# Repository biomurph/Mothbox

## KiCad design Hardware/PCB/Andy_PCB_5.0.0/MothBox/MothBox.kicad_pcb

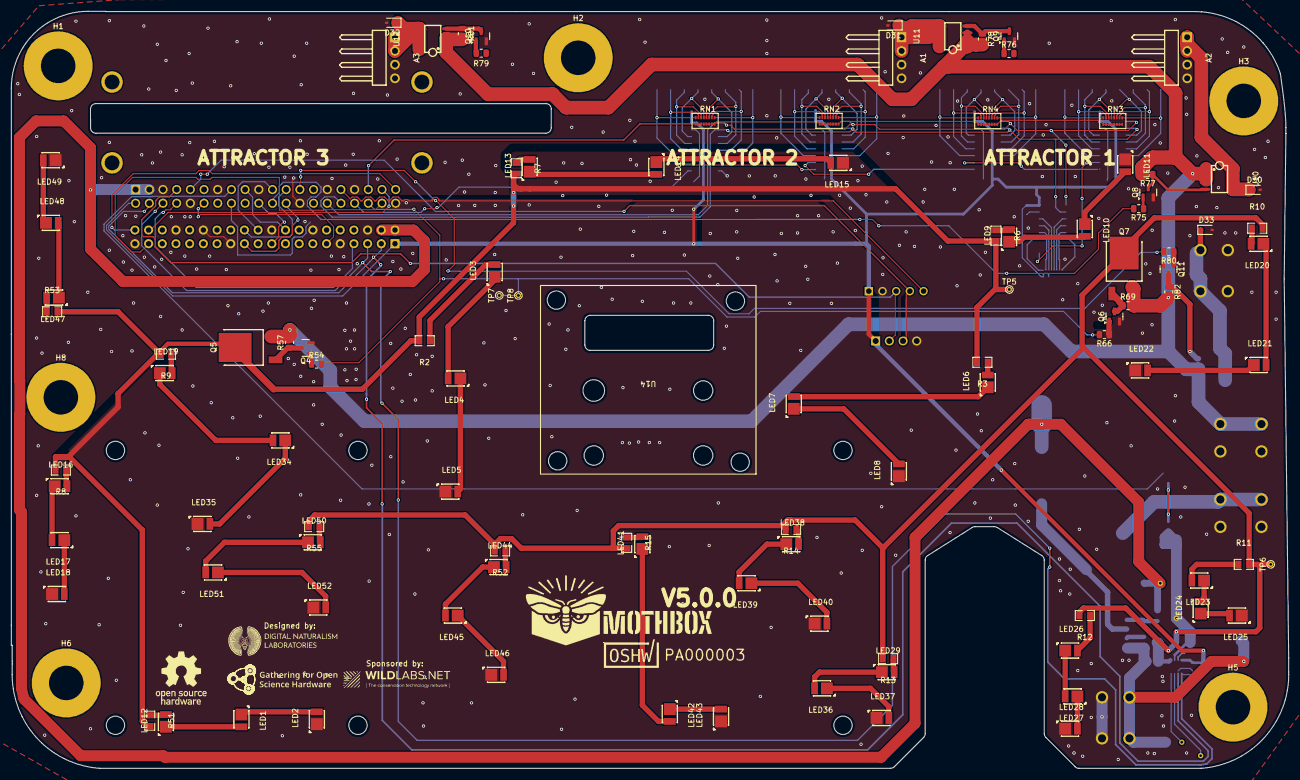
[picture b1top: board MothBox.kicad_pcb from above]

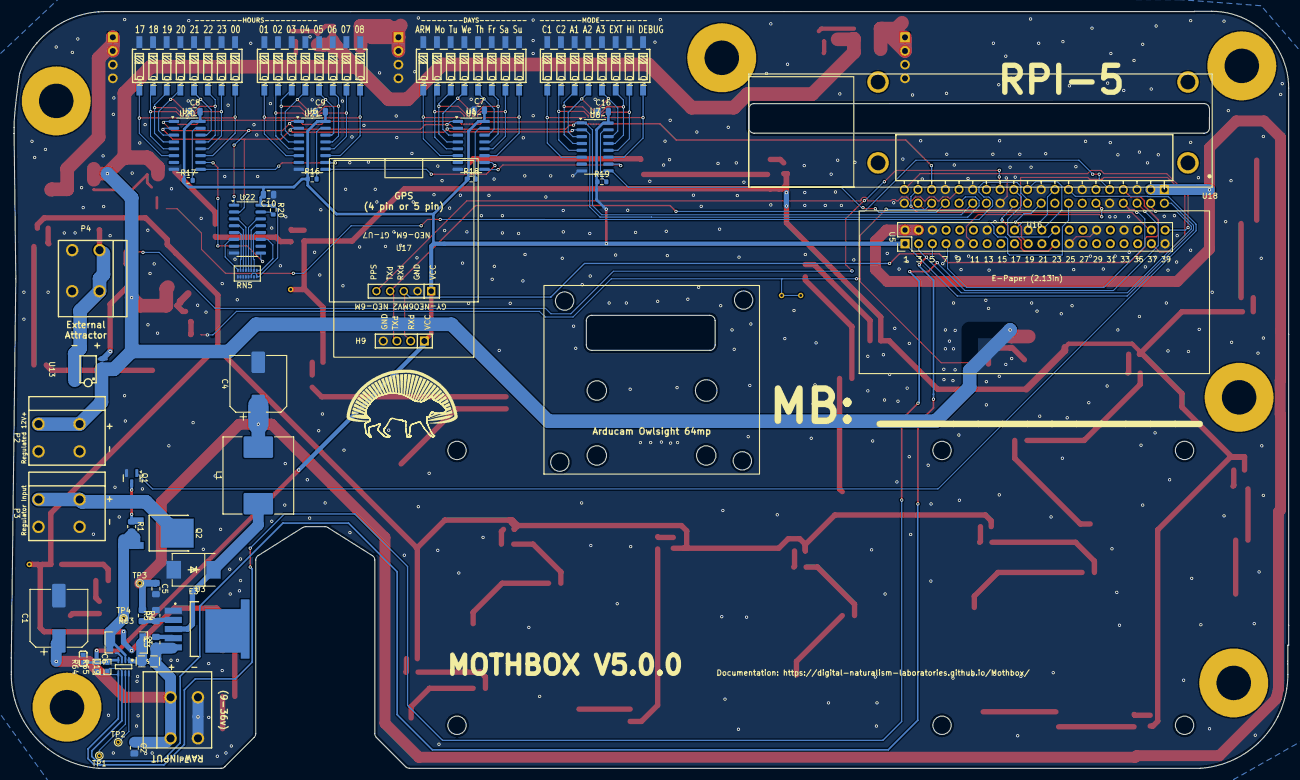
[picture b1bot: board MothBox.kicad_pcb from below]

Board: 2 copper layers, 237.0 x 140.5 mm, 163 parts (54 on the bottom side), 152 nets.

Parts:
A1, A2, A3: PZ254R-11-04P; HDR-TH_4P-P2.54-H-M-W10.4
B1: Talentcell
C1: 470uF 50V; CP_Elec_10x12.5
C2, C3, C5: 0.1uF 50V; C_0805_2012Metric_Pad1.18x1.45mm_HandSolder
C4: 330uF 50V; CP_Elec_10x10
C6: 0.1µF; C0603
C7, C8, C9, C10, C16: 0.1uF; C_0805_2012Metric
D30, D31, D32, D33: ESD12VD3B-TP; D_SOD-323
E3: SK54C; SMC_L6.9-W5.9-LS8.0-RD
F2: Polyfuse; F0805
H1, H2, H3, H5, H6, H8: MountingHole_1/4inbolt; MountingHole_6.4mm_M6_Pad
H9: GPS 4 pin 2.54-1*4P母; GPS4pin_HDR-TH_4P-P2.54-V-F
L1: 5A 47uH; L_Chilisin_BMRG00131360
LED1, LED2, LED3, LED4, LED5, LED6, LED7, LED8, LED9, LED10, LED11, LED12, LED13, LED14, LED15, LED16, LED17, LED18, LED19, LED20, LED21, LED22, LED23, LED24, LED25, LED26, LED27, LED28, LED29, LED34, LED35, LED36, LED37, LED38, LED39, LED40, LED41, LED42, LED43, LED44, LED45, LED46, LED47, LED48, LED49, LED50, LED51, LED52: XL-2835UWC-02; LED-SMD_L3.5-W2.8-RD_1.25T-2PWT
P1: Raw Input; CONN-TH_2P-P5.08_DIBO_DB142R-5.08-2P
P2: 12V Regulated Input; CONN-TH_2P-P5.08_DIBO_DB142R-5.08-2P
P3: Input to regulator; CONN-TH_2P-P5.08_DIBO_DB142R-5.08-2P
P4: External Attractor; CONN-TH_2P-P5.08_DIBO_DB142R-5.08-2P
Q1, Q4, Q6, Q8, Q9, Q10, Q11: BC817; SOT-23
Q2, Q5, Q7: SUD50P06-15-GE3; TO-252-3_L6.5-W5.8-P4.58-BL
R1, R57, R69, R77, R78, R81, R82: 10k; R_0805_2012Metric
R2, R3, R6, R7, R8, R9, R10, R11, R12, R13, R14, R15, R51, R52, R53, R55: FRC0805F30R0TS; R0805
R4: 10K; C_0805_2012Metric_Pad1.18x1.45mm_HandSolder
R5: 3.3K; C_0805_2012Metric_Pad1.18x1.45mm_HandSolder
R16, R17, R18, R19, R20: 100K; R_0603_1608Metric
R54, R66, R75, R76, R79, R80: 1k; R_0805_2012Metric
R63: 0.1/1% (PT2512FK-070R1L); R2512
R64, R65: 10k; R0603
RN1, RN2, RN3, RN4, RN5: 100K; 16P8-R-Array
TP1: A0_meas; TestPoint_THTPad_D1.0mm_Drill0.5mm
TP2: A1_meas; TestPoint_THTPad_D1.0mm_Drill0.5mm
TP3: 5V_test; TestPoint_THTPad_D1.0mm_Drill0.5mm
TP4: VIN_-; TestPoint_THTPad_D1.0mm_Drill0.5mm
TP5: +12VLED L; TestPoint_THTPad_D1.0mm_Drill0.5mm
TP6: +12VLED R; TestPoint_THTPad_D1.0mm_Drill0.5mm
TP7: LEDCTRL_L; TestPoint_THTPad_D1.0mm_Drill0.5mm
TP8: LEDCTRL_R; TestPoint_THTPad_D1.0mm_Drill0.5mm
U1: Days; SW-SMD_SMXS-08K-TP
U2: Hours1; SW-SMD_SMXS-08K-TP
U3: XL4015E1; TO-263-5_L10.2-W8.9-P1.70-TL
U5: RASPBERRY_PI_5; EPAPER_PinHeader_2x20_P2.54mm_Vertical
U6: Hours2; SW-SMD_SMXS-08K-TP
U7: Modes; SW-SMD_SMXS-08K-TP
U8, U9, U20, U21, U22: 74HC165; SOIC-16_3.9x9.9mm_P1.27mm
U10, U11, U12, U13: FDS4435BZ; SOIC-8_L5.0-W4.0-P1.27-LS6.0-BL
U14: Arducam Owlsight
U16: Female Inv Socket Pi 2.54-2*20; HDR-TH_40P-P2.54-H-F-R2-C20-W8.5
U17: GPs 5 pin PM2.54-1*5; GPS5pin_HDR-TH_5P-P2.54-V-F
U18: RASPBERRY_PI_4B_4GB; MODULE_RASPBERRY_PI_4B_4GB_Sideways
U19: INA219BIDCNT; SOT-23-8_L3.0-W1.7-P0.65-LS2.8-BR

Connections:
+3.3V: C6.2, C7.2, C8.2, C9.2, C10.2, C16.2, H9.1, R16.1, R17.1, R18.1, R19.1, R20.1, R64.2, R65.2, RN5.6 (R6.1), RN5.8 (R8.1), U5.1 (3V3), U8.16 (VCC), U9.16 (VCC), U16.2, U17.1, U19.4 (VS), U20.16 (VCC), U21.16 (VCC), U22.16 (VCC)
+5V: C4.1, C5.1, L1.2, R4.1, TP3.1, U5.2 (5V), U5.4 (5V), U16.1, U16.3
+12V: P2.2, Q5.3 (S), Q7.3 (S), R57.2, R69.2, R77.2, R78.2, R81.2, R82.2, U10.1 (S), U10.2 (S), U10.3 (S), U11.1 (S), U11.2 (S), U11.3 (S), U12.1 (S), U12.2 (S), U12.3 (S), U13.1 (S), U13.2 (S), U13.3 (S)
+24V: C1.1, C2.1, C3.1, F2.2, P1.2, U3.5 (VIN)
/GPS and Switches/Armed/Disarmed: RN2.8 (R8.1), U1.16, U9.11 (D0)
/GPS and Switches/Attractor_1: RN1.3 (R3.1), U7.11, U8.4 (D5)
/GPS and Switches/Attractor_2: RN1.4 (R4.1), U7.12, U8.3 (D4)
/GPS and Switches/Attractor_3: RN1.5 (R5.1), U7.13, U8.14 (D3)
/GPS and Switches/B0: RN5.9 (R8.2), U22.11 (D0)
/GPS and Switches/B1: RN5.10 (R7.2), U22.12 (D1)
/GPS and Switches/B2: RN5.11 (R6.2), U22.13 (D2)
/GPS and Switches/B3: RN5.12 (R5.2), U22.14 (D3)
/GPS and Switches/B4: RN5.13 (R4.2), U22.3 (D4)
/GPS and Switches/B5: RN5.14 (R3.2), U22.4 (D5)
/GPS and Switches/B6: RN5.15 (R2.2), U22.5 (D6)
/GPS and Switches/B7: RN5.16 (R1.2), U22.6 (D7)
/GPS and Switches/C1: RN1.1 (R1.1), U7.9, U8.6 (D7)
/GPS and Switches/C2: RN1.2 (R2.1), U7.10, U8.5 (D6)
/GPS and Switches/Fri: RN2.3 (R3.1), U1.11, U9.4 (D5)
/GPS and Switches/HI/LOW_PWR: RN1.7 (R7.1), U7.15, U8.12 (D1)
/GPS and Switches/Hour_1: RN3.1 (R1.1), U2.9, U20.6 (D7)
/GPS and Switches/Hour_2: RN3.2 (R2.1), U2.10, U20.5 (D6)
/GPS and Switches/Hour_3: RN3.3 (R3.1), U2.11, U20.4 (D5)
/GPS and Switches/Hour_4: RN3.4 (R4.1), U2.12, U20.3 (D4)
/GPS and Switches/Hour_5: RN3.5 (R5.1), U2.13, U20.14 (D3)
/GPS and Switches/Hour_6: RN3.6 (R6.1), U2.14, U20.13 (D2)
/GPS and Switches/Hour_7: RN3.7 (R7.1), U2.15, U20.12 (D1)
/GPS and Switches/Hour_8: RN3.8 (R8.1), U2.16, U20.11 (D0)
/GPS and Switches/Hour_9: RN4.1 (R1.1), U6.9, U21.6 (D7)
/GPS and Switches/Hour_10: RN4.2 (R2.1), U6.10, U21.5 (D6)
/GPS and Switches/Hour_11: RN4.3 (R3.1), U6.11, U21.4 (D5)
/GPS and Switches/Hour_12: RN4.4 (R4.1), U6.12, U21.3 (D4)
/GPS and Switches/Hour_13: RN4.5 (R5.1), U6.13, U21.14 (D3)
/GPS and Switches/Hour_14: RN4.6 (R6.1), U6.14, U21.13 (D2)
/GPS and Switches/Hour_15: RN4.7 (R7.1), U6.15, U21.12 (D1)
/GPS and Switches/Hour_16: RN4.8 (R8.1), U6.16, U21.11 (D0)
/GPS and Switches/INT/EXT_Attractor: RN1.6 (R6.1), U7.14, U8.13 (D2)
/GPS and Switches/Mon: RN2.7 (R7.1), U1.15, U9.12 (D1)
/GPS and Switches/Sat: RN2.2 (R2.1), U1.10, U9.5 (D6)
/GPS and Switches/Sun: RN2.1 (R1.1), U1.9, U9.6 (D7)
/GPS and Switches/Test_Debug: RN1.8 (R8.1), U7.16, U8.11 (D0)
/GPS and Switches/Thur: RN2.4 (R4.1), U1.12, U9.3 (D4)
/GPS and Switches/Tue: RN2.6 (R6.1), U1.14, U9.13 (D2)
/GPS and Switches/U9_OUT: U8.10 (DS), U9.9 (Q7)
/GPS and Switches/U20_OUT: U20.9 (Q7), U21.10 (DS)
/GPS and Switches/U21_OUT: U9.10 (DS), U21.9 (Q7)
/GPS and Switches/U22_OUT: U20.10 (DS), U22.9 (Q7)
/GPS and Switches/Wed: RN2.5 (R5.1), U1.13, U9.14 (D3)
/Photo LED's/+12V_L_LED: Q5.2 (D), R2.2, R3.2, R6.2, R7.2, R8.2, R9.2, R51.2, R53.2, TP5.1
/Photo LED's/+12V_R_LED: Q7.2 (D), R10.2, R11.2, R12.2, R13.2, R14.2, R15.2, R52.2, R55.2, TP6.1
/Power/FB: R4.2, R5.1, U3.2 (FB)
/Power/VIN+: F2.1, R63.2, U19.1 (IN+)
/Power/VIN-: Q2.3 (S), R1.2, R63.1, TP4.1, U19.2 (IN-)
/RPI5/GPIO4/GPIO_GCKL: U5.7 (GPIO4/GPIO_GCKL), U16.8
/RPI5/Save for eink_11: U5.11 (GPIO17/GPIO_GEN0), U16.12
/RPI5/Save for eink_18: U5.18 (GPIO24/GPIO_GEN5), U16.17
/RPI5/Save for eink_19: U5.19 (GPIO10/SPI_MOSI), U16.20
/RPI5/Save for eink_22: U5.22 (GPIO25/GPIO_GEN6), U16.21
/RPI5/Save for eink_23: U5.23 (GPIO11/SPI_SCLK), U16.24
/RPI5/Save for eink_24: U5.24 (GPIO8/~SPI_CE0), U16.23
/RPI5/Save for relay: U5.38 (GPIO20), U16.37
/RPI5/Save for relay 2: U5.40 (GPIO21), U16.39
/RPI5/Save for relay 3: U5.37 (GPIO26), U16.38
/UV LED PCB/+12V_PCB1: A2.1, A2.2, D30.1 (K), U10.5 (D), U10.6 (D), U10.7 (D), U10.8 (D)
/UV LED PCB/+12V_PCB2: A1.1, A1.2, D31.1 (K), U11.5 (D), U11.6 (D), U11.7 (D), U11.8 (D)
/UV LED PCB/+12V_PCB3: A3.1, A3.2, D32.1 (K), U12.5 (D), U12.6 (D), U12.7 (D), U12.8 (D)
/UV LED PCB/+12V_PCB4: D33.1 (K), P4.2, U13.5 (D), U13.6 (D), U13.7 (D), U13.8 (D)
EN_12VReg: Q1.1 (B), U16.15
GND: A1.3, A1.4, A2.3, A2.4, A3.3, A3.4, C1.2, C2.2, C4.2, C5.2, C6.1, C7.1, C8.1, C9.1, C10.1, C16.1, D30.2 (A), D31.2 (A), D32.2 (A), D33.2 (A), E3.2 (A), H9.4, LED2.1 (K), LED5.1 (K), LED8.1 (K), LED11.1 (K), LED15.1 (K), LED18.1 (K), LED22.1 (K), LED25.1 (K), LED28.1 (K), LED35.1 (K), LED37.1 (K), LED40.1 (K), LED43.1 (K), LED46.1 (K), LED49.1 (K), LED52.1 (K), P1.1, P2.1, P3.1, P4.1, Q1.2 (E), Q4.2 (E), Q6.2 (E), Q8.2 (E), Q9.2 (E), Q10.2 (E), Q11.2 (E), R5.2, RN5.1 (R1.1), RN5.2 (R2.1), RN5.3 (R3.1), RN5.4 (R4.1), RN5.5 (R5.1), RN5.7 (R7.1), U1.1, U1.2, U1.3, U1.4, U1.5, U1.6, U1.7, U1.8, U2.1, U2.2, U2.3, U2.4, U2.5, U2.6, U2.7, U2.8, U3.1 (GND), U5.6 (GND), U5.9 (GND), U5.14 (GND), U5.20 (GND), U5.25 (GND), U5.30 (GND), U5.34 (GND), U5.39 (GND), U6.1, U6.2, U6.3, U6.4, U6.5, U6.6, U6.7, U6.8, U7.1, U7.2, U7.3, U7.4, U7.5, U7.6, U7.7, U7.8, U8.8 (GND), U9.8 (GND), U16.5, U16.10, U16.13, U16.19, U16.26, U16.29, U16.33, U16.40, U17.2, U19.3 (GND), U20.8 (GND), U21.8 (GND), U22.8 (GND)
GPS_PPS: U16.31, U17.5
GPS_RX: H9.2, U16.7, U17.3
GPS_TX: H9.3, U16.9, U17.4
L_LED_CTRL: R54.2, R66.2, TP7.1, TP8.1, U16.36
unnamed: E3.1 (C), L1.1, U3.3 (SW)
unnamed: LED1.2 (A), LED12.1 (K)
unnamed: LED1.1 (K), LED2.2 (A)
unnamed: LED3.2 (A), R2.1
unnamed: LED3.1 (K), LED4.2 (A)
unnamed: LED4.1 (K), LED5.2 (A)
unnamed: LED6.2 (A), R3.1
unnamed: LED6.1 (K), LED7.2 (A)
unnamed: LED7.1 (K), LED8.2 (A)
unnamed: LED9.2 (A), R6.1
unnamed: LED9.1 (K), LED10.2 (A)
unnamed: LED10.1 (K), LED11.2 (A)
unnamed: LED12.2 (A), R51.1
unnamed: LED13.2 (A), R7.1
unnamed: LED13.1 (K), LED14.2 (A)
unnamed: LED14.1 (K), LED15.2 (A)
unnamed: LED16.2 (A), R8.1
unnamed: LED16.1 (K), LED17.2 (A)
unnamed: LED17.1 (K), LED18.2 (A)
unnamed: LED19.2 (A), R9.1
unnamed: LED19.1 (K), LED34.2 (A)
unnamed: LED20.2 (A), R10.1
unnamed: LED20.1 (K), LED21.2 (A)
unnamed: LED21.1 (K), LED22.2 (A)
unnamed: LED23.2 (A), R11.1
unnamed: LED23.1 (K), LED24.2 (A)
unnamed: LED24.1 (K), LED25.2 (A)
unnamed: LED26.2 (A), R12.1
unnamed: LED26.1 (K), LED27.2 (A)
unnamed: LED27.1 (K), LED28.2 (A)
unnamed: LED29.2 (A), R13.1
unnamed: LED29.1 (K), LED36.2 (A)
unnamed: LED34.1 (K), LED35.2 (A)
unnamed: LED36.1 (K), LED37.2 (A)
unnamed: LED38.2 (A), R14.1
unnamed: LED38.1 (K), LED39.2 (A)
unnamed: LED39.1 (K), LED40.2 (A)
unnamed: LED41.2 (A), R15.1
unnamed: LED41.1 (K), LED42.2 (A)
unnamed: LED42.1 (K), LED43.2 (A)
unnamed: LED44.2 (A), R52.1
unnamed: LED44.1 (K), LED45.2 (A)
unnamed: LED45.1 (K), LED46.2 (A)
unnamed: LED47.2 (A), R53.1
unnamed: LED47.1 (K), LED48.2 (A)
unnamed: LED48.1 (K), LED49.2 (A)
unnamed: LED50.2 (A), R55.1
unnamed: LED50.1 (K), LED51.2 (A)
unnamed: LED51.1 (K), LED52.2 (A)
unnamed: Q1.3 (C), Q2.1 (G), R1.1
unnamed: P3.2, Q2.2 (D)
unnamed: Q4.1 (B), R54.1
unnamed: Q4.3 (C), Q5.1 (G), R57.1
unnamed: Q6.1 (B), R66.1
unnamed: Q6.3 (C), Q7.1 (G), R69.1
unnamed: Q8.1 (B), R75.1
unnamed: Q8.3 (C), R77.1, U10.4 (G)
unnamed: Q9.1 (B), R76.1
unnamed: Q9.3 (C), R78.1, U11.4 (G)
unnamed: Q10.1 (B), R79.1
unnamed: Q10.3 (C), R81.1, U12.4 (G)
unnamed: Q11.1 (B), R80.1
unnamed: Q11.3 (C), R82.1, U13.4 (G)
unnamed: C3.2, U3.4 (VC)
unnamed: R19.2, U8.15 (~CE)
unnamed: R18.2, U9.15 (~CE)
unnamed: TP1.1, U19.7 (A0)
unnamed: TP2.1, U19.8 (A1)
unnamed: R17.2, U20.15 (~CE)
unnamed: R16.2, U21.15 (~CE)
unnamed: R20.2, U22.15 (~CE)
SCL: R64.1, U5.5 (GPIO3/SCL1), U16.6, U19.5 (SCL)
SDA: R65.1, U5.3 (GPIO2/SDA1), U16.4, U19.6 (SDA)
SHIFT_CLOCK: U8.2 (CP), U9.2 (CP), U16.32, U20.2 (CP), U21.2 (CP), U22.2 (CP)
SHIFT_LOAD: U8.1 (~PL), U9.1 (~PL), U16.30, U20.1 (~PL), U21.1 (~PL), U22.1 (~PL)
SHIFT_OUT: U8.9 (Q7), U16.34
SWITCH_ENABLE: RN1.9 (R8.2), RN1.10 (R7.2), RN1.11 (R6.2), RN1.12 (R5.2), RN1.13 (R4.2), RN1.14 (R3.2), RN1.15 (R2.2), RN1.16 (R1.2), RN2.9 (R8.2), RN2.10 (R7.2), RN2.11 (R6.2), RN2.12 (R5.2), RN2.13 (R4.2), RN2.14 (R3.2), RN2.15 (R2.2), RN2.16 (R1.2), RN3.9 (R8.2), RN3.10 (R7.2), RN3.11 (R6.2), RN3.12 (R5.2), RN3.13 (R4.2), RN3.14 (R3.2), RN3.15 (R2.2), RN3.16 (R1.2), RN4.9 (R8.2), RN4.10 (R7.2), RN4.11 (R6.2), RN4.12 (R5.2), RN4.13 (R4.2), RN4.14 (R3.2), RN4.15 (R2.2), RN4.16 (R1.2), U16.35
UV1_CTRL: R75.2, U16.22
UV4_EX_CTRL: R80.2, U16.25

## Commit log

2025-06-23 update gitignore
2025-06-23 Tidied up and merged with local main
